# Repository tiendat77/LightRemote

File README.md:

# Light Remote Project
> Remote control home appliances by smartphone

The purpose of this project is build an android-app to control home appliances.

## Requirements
1. ESP8266 Module
2. Android phone running 5.0 (Lollipop) or higher
3. WiFi network

## Create a Telegram bot for ESP8266 board

Open Telegram and follow the next steps to create a Telegram Bot:

1. Search for “botfather” and click the BotFather as shown below. Or open this link t.me/botfather in your smartphone.

2. Type /newbot and follow the instructions to create your bot. Give it a name and username.

3. If your bot is successfully created, you’ll receive a message with a link to access the bot and the bot token. Save the bot token because you’ll need it so that the ESP8266 can interact with the bot.

## Preparing Arduino IDE
To install the ESP32 board in your Arduino IDE, follow these next instructions:
1. In Arduino IDE, go to File> Preferences.
2. Enter `https://dl.espressif.com/dl/package_esp32_index.json` into the “Additional Board Manager URLs” field as shown in the figure below. Then, click the “OK” button.

    **Note**: if you already have the boards URL, you can separate the URLs with a comma.

3. Open the Boards Manager. Go to Tools > Board > Boards Manager…
4. Search for ESP32 and press install button for the “ESP32 by Espressif Systems“.
5. That’s it. It should be installed after a few seconds.

You also have to install Universal Telegram Bot Library and ArduinoJson Library. Follow the next steps to install the library from zip file:
1. Download [Universal Telegram Bot](https://github.com/tiendat77/LightRemote/blob/master/esp8266/libraries/Universal-Arduino-Telegram-Bot.zip) and [ArduinoJson](https://github.com/tiendat77/LightRemote/blob/master/esp8266/libraries/ArduinoJson.zip)
2. Open Sketch > Include Library > Add.ZIP Library...
3. Add the library you’ve just downloaded.

## ESP8266
[Arduino Library](https://github.com/esp8266/Arduino)

Connection:
| PIN          | Device    | Description        |
| -----------  | --------- | ------------------ |
| GPIO12       | Light 1   | Light 1 control    |
| GPIO13       | Light 2   | Light 2 control    |
| GPIO15       | LED       | Show wifi signal status |

## Usage
1. Upload [the sketch](https://github.com/tiendat77/LightRemote/blob/master/esp8266/webserver/) to the ESP8266 via [Arduino IDE](https://www.arduino.cc/en/software)
2. Install [Light Remote](https://github.com/tiendat77/LightRemote/blob/master/LightRemote.apk) application to your smartphone
3. Connect ESP8266 and your smartphone to the same WiFi network
4. Open Light Remote application, then open *App Settings* and make sure *ESP Address* is correct.
5. Enjoy!

## Demos :boom:

## Open source libraries
- [Universal Telegram Bot Library](https://github.com/witnessmenow/Universal-Arduino-Telegram-Bot)
- [ArduinoJson Library](https://github.com/bblanchon/ArduinoJson)

## License

MIT © 2020 [TienDat](mailto:huynhztienzdat@gmail.com), see [the license](https://github.com/tiendat77/LightRemote/blob/master/LICENSE).

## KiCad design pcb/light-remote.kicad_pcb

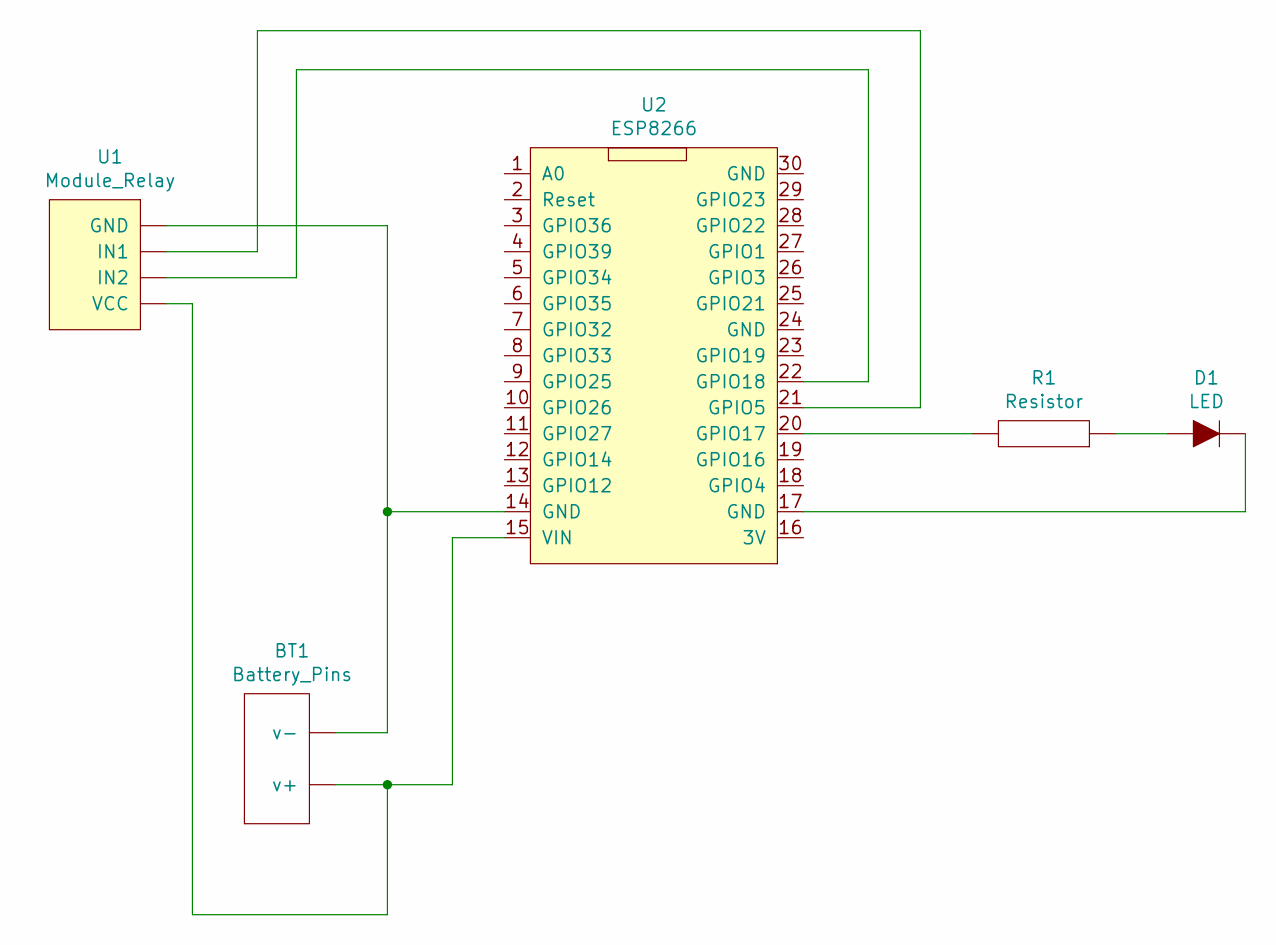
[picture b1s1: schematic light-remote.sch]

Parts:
BT1: Battery_Pins; Domino_2_5.05mm
D1: LED; Led
R1: Resistor
U1: Module_Relay
U2: ESP8266; ESP8266_Node

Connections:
unnamed: BT1.1 (v+), U1.4 (VCC), U2.15 (VIN)
unnamed: BT1.2 (v-), U1.1 (GND), U2.14 (GND)
unnamed: D1.1, R1.1
unnamed: D1.2, U2.17 (GND)
unnamed: R1.2, U2.20 (GPIO17)
unnamed: U1.2 (IN1), U2.21 (GPIO5)
unnamed: U1.3 (IN2), U2.22 (GPIO18)

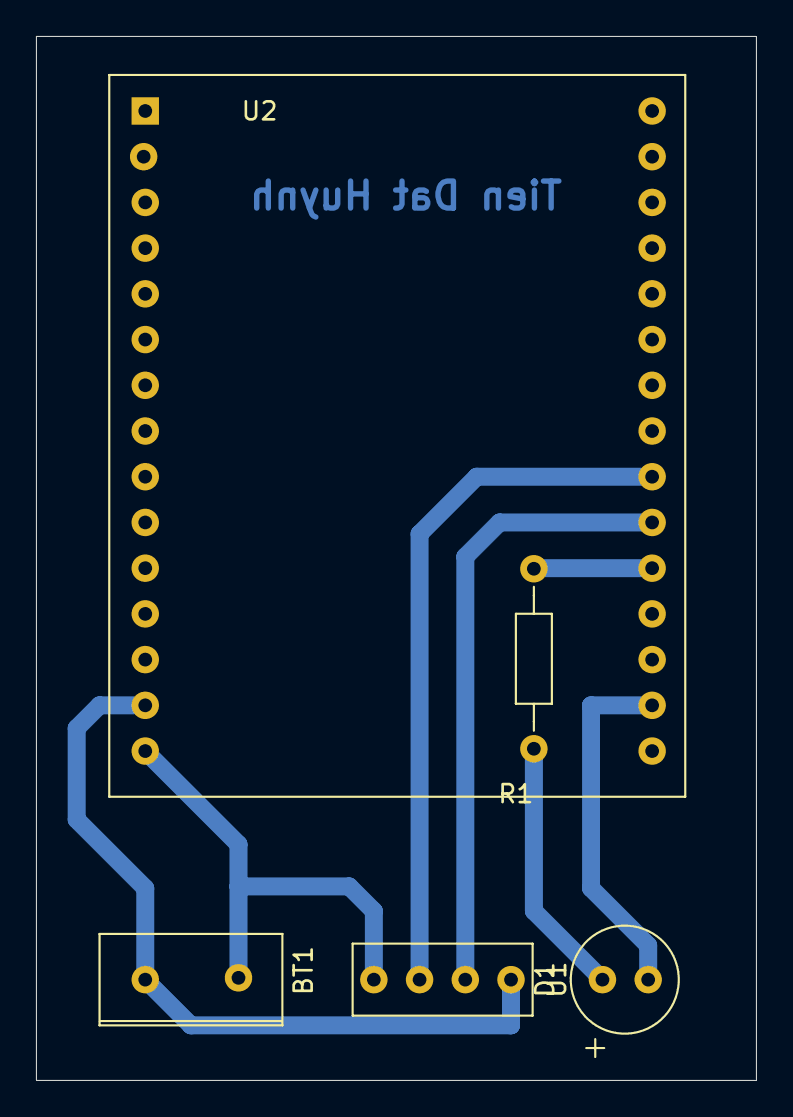
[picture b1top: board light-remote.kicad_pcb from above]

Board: 2 copper layers, 40.0 x 58.0 mm, 5 parts (0 on the bottom side), 7 nets.

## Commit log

2020-04-05 import ir library; add bottom navigation
2020-04-05 design view model (wifi and infrared)
2020-04-05 add retrofit and server test
2020-04-06 update retrofit
2020-04-06 make esp8266 as web server
2020-04-06 update api service
2020-04-07 test preference and update color
2020-04-08 update share preference and icon
2020-04-10 update esp8266 web server handler
2020-04-11 update embedded (#1)
    * update README
    * update README
    * update esp8266 web server handler
    * update README
2020-04-15 update(esp): web server handler
2020-04-15 update(app): add app icon and generate apk
2020-04-15 merge develop
    * update(esp): web server handler
    * update(app): add app icon and generate apk
2020-04-18 update esp web server
2020-05-19 update layout
2020-05-20 use static ip for esp8266
2020-12-30 telegram chat bot
2020-12-31 chore
2021-01-12 feat: pcb
2021-01-17 feat: esp8266 web server
2021-01-17 feat: doc
